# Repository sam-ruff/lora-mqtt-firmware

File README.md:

# LoRaMqttHub

Firmware that turns the Walkie-Textie radio board (ESP32-S3 + Wio-SX1262) into
a mains-powered hub. It has two operating modes, selected by configuration:

- **Bridge**: receives Walkie-Textie LoRa packets and publishes them to an
  MQTT broker over WiFi, and transmits packets published to its command topic.
- **LoRaWAN gateway**: a single-channel Semtech UDP packet forwarder for a
  LoRaWAN network server such as ChirpStack.

Pure Rust, no C: esp-hal + esp-rtos (Embassy executor), esp-radio for WiFi,
a hand-written SX1262 driver, embassy-net and rust-mqtt. The shared wire
protocol lives in the [`wt-protocol`](https://github.com/sam-ruff/walkie-textie-protocol)
submodule, so clone with `--recursive`.

## Building and flashing

```bash
cargo install espup espflash
espup install
source "$HOME/export-esp.sh"

cargo +esp build --features embedded --release -Zbuild-std=core,alloc
./flash_devices.sh          # build + flash all connected boards
```

After flashing, power-cycle the board (unplug and replug, do not hold BOOT).
The ESP32-S3 native USB-Serial-JTAG cannot be reset into the application from
the host, so the board stays in ROM download mode until power-cycled. A
running hub enumerates as "LoRaMqttHub" with USB serial `LMH-XXXXXX`
and exposes two CDC ports: data (interface 0) and debug log (interface 2).
The running app owns the USB port, so reflashing needs the board back in
bootloader mode first (hold BOOT while plugging in).

espflash reads `espflash.toml` from the working directory. If it names a
bootloader binary that does not exist, flashing fails with a misleading
"Error while connecting to device" - the file ships with the override
commented out and the stock espflash bootloader is used.

## Configuration

An unprovisioned hub (no WiFi credentials) starts its own open hotspot,
`LoRaMqttHub-XXXXXX`. Join it with a phone and the captive portal at
`http://192.168.4.1` opens: set the WiFi network, MQTT broker, operating mode
and gateway settings, save, and the hub restarts onto your network. The same
portal appears again if the configured network stays unreachable (wrong
password, network gone), so a hub can always be re-provisioned without a
cable. The portal also serves a JSON API (`GET/POST /api/config`,
`GET /api/status`) for app-driven setup.

Defaults can also be baked at build time through environment variables, all
optional: `HUB_WIFI_SSID`, `HUB_WIFI_PASSWORD`, `HUB_MQTT_HOST`,
`HUB_MQTT_PORT`, `HUB_MQTT_CLIENT_ID`, `HUB_MODE` (`bridge` or `gateway`),
`HUB_GW_HOST`, `HUB_GW_PORT`.

Runtime provisioning also works over the USB data port with hub commands
layered on the Walkie-Textie wire protocol (COBS-framed, CRC-16, see
`hub-protocol/`): set WiFi credentials, MQTT broker, gateway settings and
mode; read back the configuration (the WiFi password is never echoed) and
live status (link states, IP, counters, uptime). Settings persist in the
`nvs` flash partition and apply on the next boot, so the flow is set, then
reboot.

## Bridge mode

Topics live under `wt/hub/<id>/` where `<id>` is the hex device id from the
USB serial:

- `rx`: received LoRa packets, JSON with `payload_hex`, `rssi`, `snr`, `seq`
  and `uptime_ms`.
- `tx`: publish `{"payload_hex":"...","id":123}` here to transmit over LoRa;
  `id` is optional and echoed back.
- `tx/result`: `{"result":"sent"|"refused"|"error"...}` per downlink, with
  `retry_after_secs` when the EU duty cycle budget refuses a transmission.
- `status`: retained `{"online":true,...}`, with an offline last-will.

The broker connection is plain TCP (local broker assumed); the client id
defaults to `wt-hub-<id>`.

## LoRaWAN gateway mode

Speaks the Semtech UDP packet-forwarder protocol to a network server -
typically the ChirpStack gateway bridge on port 1700. The gateway EUI derives
from the MAC address with the standard FFFE insertion.

An SX1262 is a single-channel, half-duplex radio, which makes this a
single-channel gateway with real limitations:

- Only uplinks on the configured frequency and spreading factor are heard
  (default 868.1 MHz, SF7BW125). OTAA joins hop across three channels, so
  pin devices to the gateway channel and disable ADR in the device profile.
- The radio is deaf while transmitting a downlink.
- The Things Network discourages single-channel gateways; use a self-hosted
  ChirpStack.

Downlinks obey the EU duty cycle per sub-band and are refused with a
`DUTY_CYCLE_OVERFLOW` TX_ACK when the hourly budget is spent. The gateway is
payload-agnostic: joins, MICs and encryption all happen at the network server.

## Configurator app

`app/` holds a Flutter app for phones that drives the same provisioning API
as the captive portal: join the hub's hotspot, open the app, connect and set
everything up. The HTTP client and validation live in a Rust engine
(`app/rust_backend/`) exposed through flutter_rust_bridge, mirroring the
Walkie-Textie messenger app's architecture: `./build_rust.sh` regenerates the
bindings and builds the engine, Android cross-compiles it via cargo-ndk from
Gradle, and iOS links a static xcframework built by `tool/build_ios_libs.sh`.

```bash
cd app
./build_rust.sh
flutter run --dart-define=MOCK=true    # full flow against a fake hub, no hardware
flutter run                            # against a real hub
```

## Testing

Host tests need no hardware:

```bash
cargo test --features host-test --target x86_64-unknown-linux-gnu
cargo test --manifest-path hub-protocol/Cargo.toml --target x86_64-unknown-linux-gnu
cargo test --manifest-path vendor/wt-protocol/Cargo.toml --target x86_64-unknown-linux-gnu
```

Hardware tests run from `integration_tests/` against flashed boards:

```bash
cargo integration     # serial host-link, one board
cargo lora            # two boards over the air
cargo duty            # duty cycle lockout (spends ~6 min of airtime)
cargo hub -- --wifi-ssid <ssid> --wifi-password <pw> --broker-host <ip>
cargo gateway -- --server-host <this machine's LAN IP>
```

`cargo hub` needs a hub board, a node board and a reachable MQTT broker; it
provisions the hub, then proves both bridge directions end to end.
`cargo gateway` binds the network-server side itself and verifies the
forwarder protocol against the live gateway. Watch the debug CDC port
(115200 baud) for the firmware's own view of events.

For a Bluetooth-only node, `cargo ble-e2e` exchanges real messages across
the whole chain (BLE to the node, LoRa over the air, hub, MQTT broker) in
both directions, with a soak loop and failure-path checks. `cargo
hub-status` prints the hub's live state over serial, and `--clear` factory
resets it back to the provisioning hotspot.

The browser-driven portal tests live in `e2e/`: `run_e2e.sh` joins the
hub's hotspot with nmcli, runs the Playwright suite on desktop and mobile
viewports, provisions the hub through the real UI and rejoins your network.

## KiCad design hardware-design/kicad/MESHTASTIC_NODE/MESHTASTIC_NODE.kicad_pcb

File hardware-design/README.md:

# Hardware design

PCB design and tooling for the MESHTASTIC NODE board (ESP32-S3 + Wio-SX1262 LoRa).
There are two design states:

- `Production Files/` - the original as-built 4-layer manufacturing outputs. Send
  these straight to a fab if you just want the existing board made.
- `kicad/MESHTASTIC_NODE/` - an editable 4-layer KiCad project, generated entirely
  from scripts in `tools/` so a schematic edit reproduces a full production package.

Generated views live in `diagrams/`, component datasheets and a spec digest in
`datasheets/`, and helper scripts in `tools/`.

## Schematic-to-production pipeline

The whole flow is one command (needs the KiCad AppImage and the freerouting jar -
see "Routing toolchain" below):

```bash
python3 tools/build_all.py            # schematic -> board -> route -> kicad/fab/
```

It runs, and gates on, each stage: regenerate the schematic
(`build_schematic.py`), ERC, verify every firmware net (`verify_nets.py`), build
the 4-layer board (`board_setup.py` + `build_board.py`), check placement
(`check_placement.py`), autoroute + finish + pour ground/power planes
(`route.py`), DRC (must be 0 errors / 0 unconnected / parity-clean), then export
the Gerbers, drill, CPL and BOM (`fab_outputs.py`). Upload
`kicad/fab/gerbers.zip` plus `BOM.csv` and `CPL.csv` to PCBWay.

To change the board, edit the net map in `tools/build_schematic.py` (and the
placement overrides in `tools/placement.py` if a part needs moving), then re-run
`build_all.py`. Use `--skip-route` to re-check and re-export the current routed
board without re-routing.

### Routing toolchain

`tools/route.py` exports a Specctra DSN with the bundled `pcbnew`, autoroutes the
signals with freerouting (headless), imports the SES back, closes any stragglers
(`finish_route.py`), then pours the GND/+3V3 planes and stitching vias
(`pour.py`). Install freerouting once:

```bash
mkdir -p ~/.local/share/freerouting
curl -L -o ~/.local/share/freerouting/freerouting-2.2.4.jar \
  https://github.com/freerouting/freerouting/releases/download/v2.2.4/freerouting-2.2.4.jar
```

Override the tool paths with the `KICAD_APPIMAGE` and `FREEROUTING_JAR` env vars.

## Tools to install first

Commands assume Ubuntu Linux. `uv` and Node.js are expected to be present already.

### KiCad 9 or newer (required)

Provides `kicad-cli`, the GUI editors, and the bundled ngspice/3D tools. The
design was authored in 9.0.1, and the headless DRC/ERC checks need v9+; KiCad 7
(the default in some Ubuntu repos) cannot open v9 files or run the CLI checks.

```bash
# option 1 - PPA (needs sudo)
sudo add-apt-repository ppa:kicad/kicad-9.0-releases
sudo apt update && sudo apt install --install-recommends kicad

# option 2 - Flatpak (no sudo)
flatpak install --user flathub org.kicad.KiCad
flatpak run --command=kicad-cli org.kicad.KiCad version

# option 3 - AppImage (no sudo) - the method in use here
# download the KiCad AppImage, put it on a writeable PATH dir, and add a wrapper
# that dispatches the bundled CLI (the AppImage selects its tool from the first arg):
mv kicad-*-x86_64.AppImage ~/.local/bin/ && chmod +x ~/.local/bin/kicad-*.AppImage
printf '#!/bin/sh\nexec "$HOME/.local/bin/kicad-10.0.3-x86_64.AppImage" kicad-cli "$@"\n' > ~/.local/bin/kicad-cli
printf '#!/bin/sh\nexec "$HOME/.local/bin/kicad-10.0.3-x86_64.AppImage" kicad "$@"\n' > ~/.local/bin/kicad
chmod +x ~/.local/bin/kicad-cli ~/.local/bin/kicad
```

For headless 3D board renders also install `xvfb`.

### Diagram rendering

```bash
# block / component-overview diagrams (needs Node.js + Chrome/Chromium)
npm install -g @mermaid-js/mermaid-cli
# rendering points Puppeteer at the system Chrome via tools/puppeteer-config.json

# to-scale placement diagram
uv pip install matplotlib
```

### Gerber inspection (no KiCad source needed)

```bash
uv tool install gerbonara      # render Gerbers to SVG
uvx cairosvg in.svg -o out.png -s 3   # rasterise SVG to PNG so it can be viewed
```

## Regenerating diagrams

See the top-level `CLAUDE.md` for the regeneration commands and the readability
checklist that must pass before a diagram change is considered done.

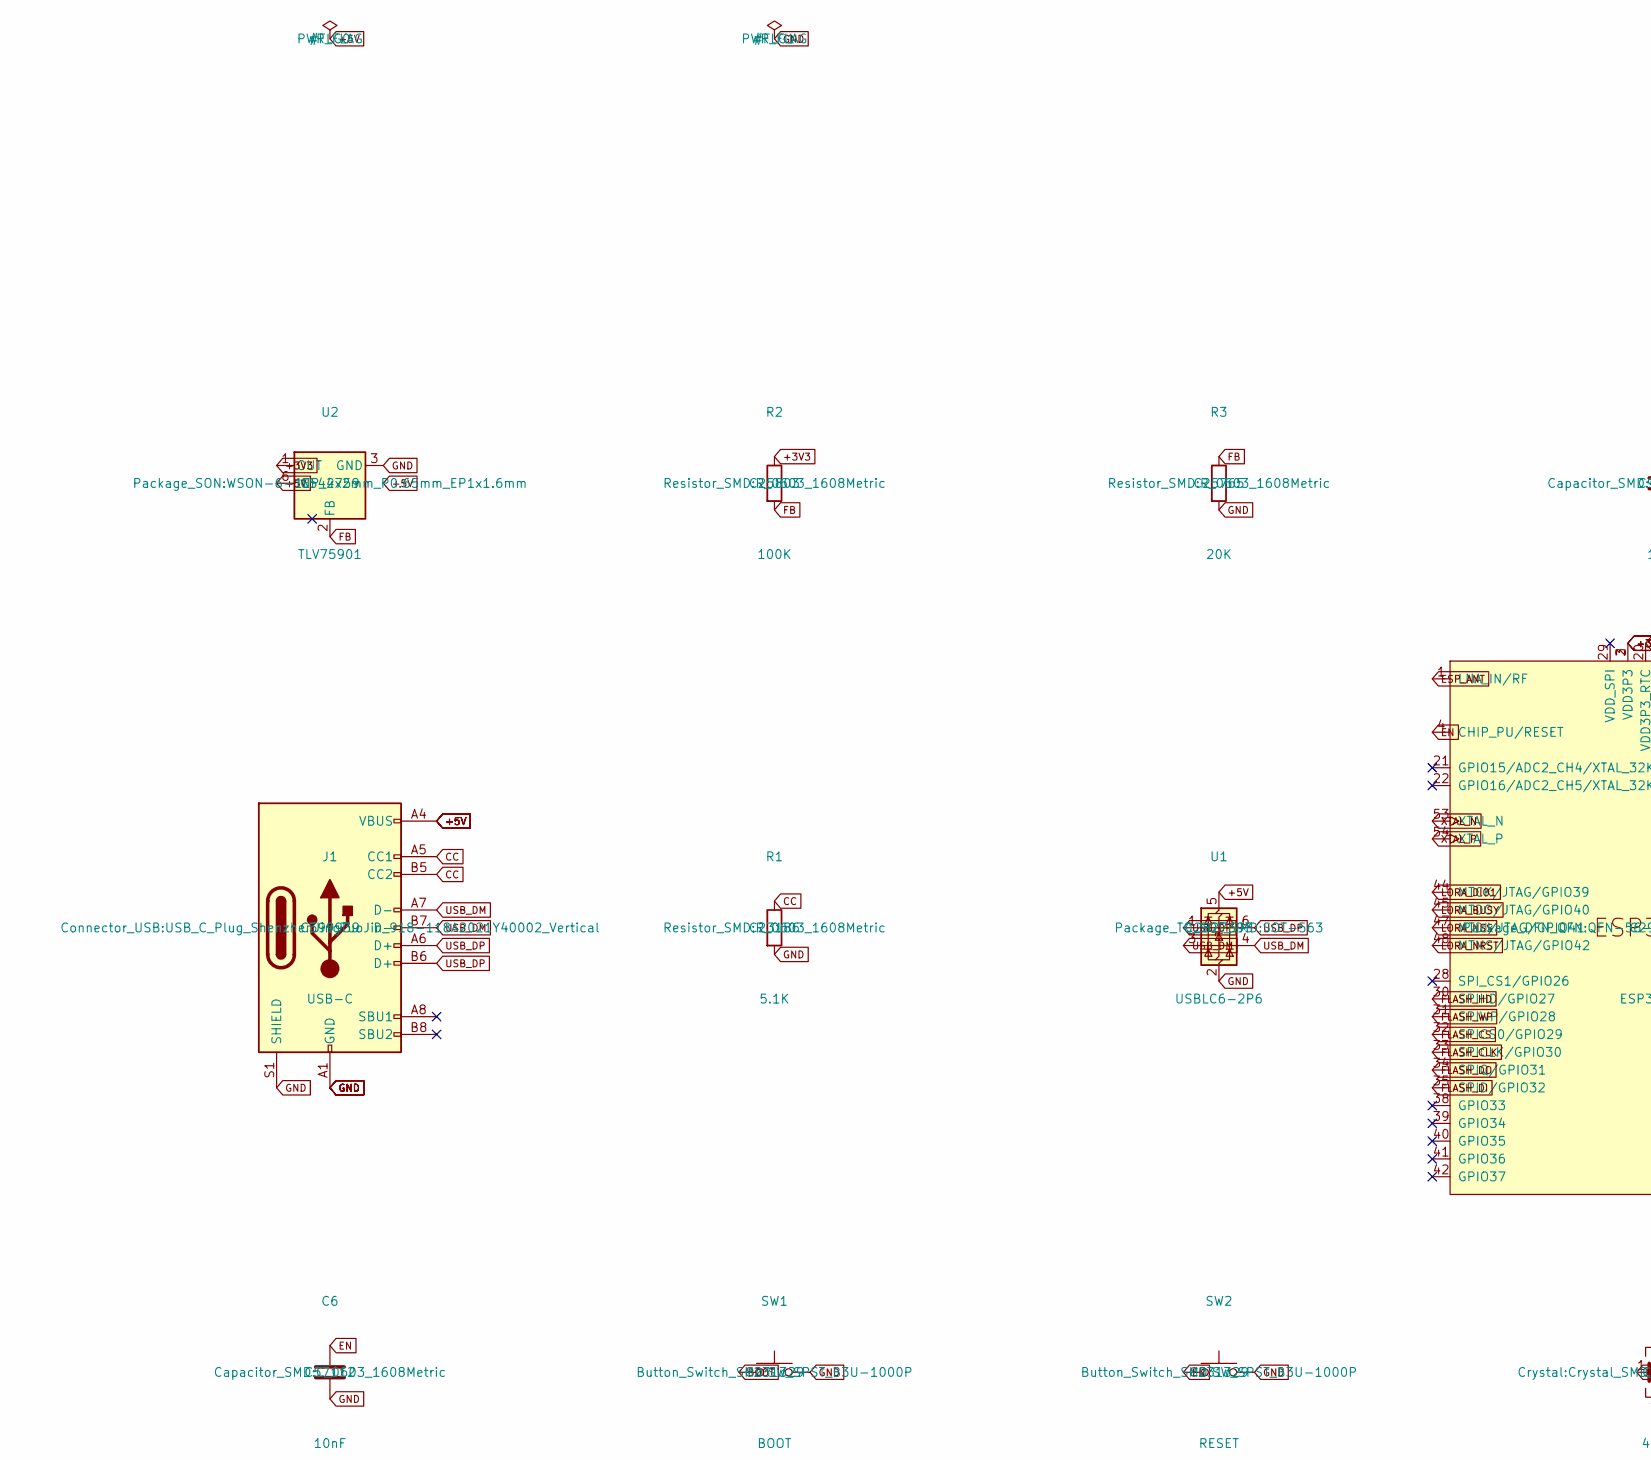
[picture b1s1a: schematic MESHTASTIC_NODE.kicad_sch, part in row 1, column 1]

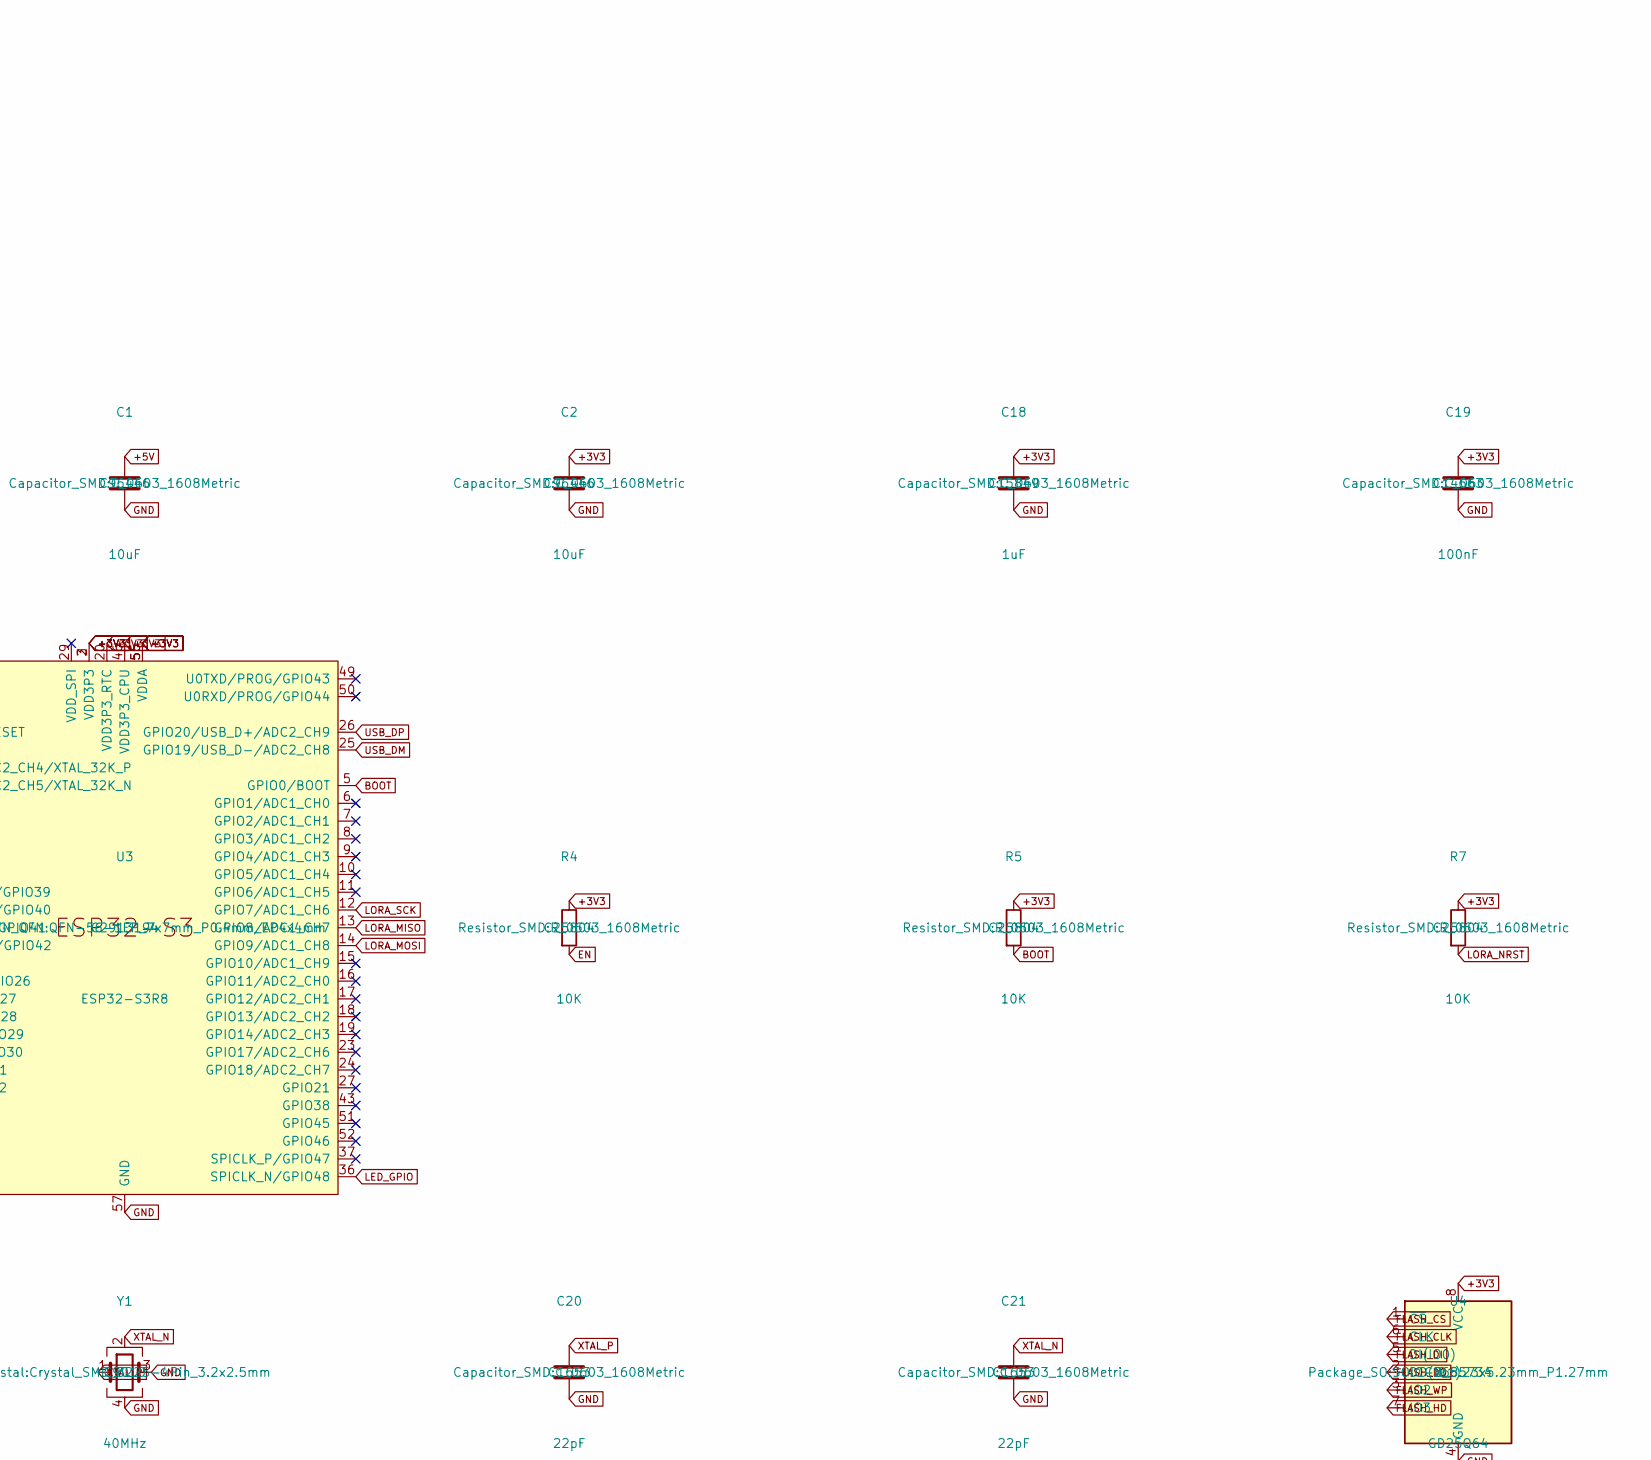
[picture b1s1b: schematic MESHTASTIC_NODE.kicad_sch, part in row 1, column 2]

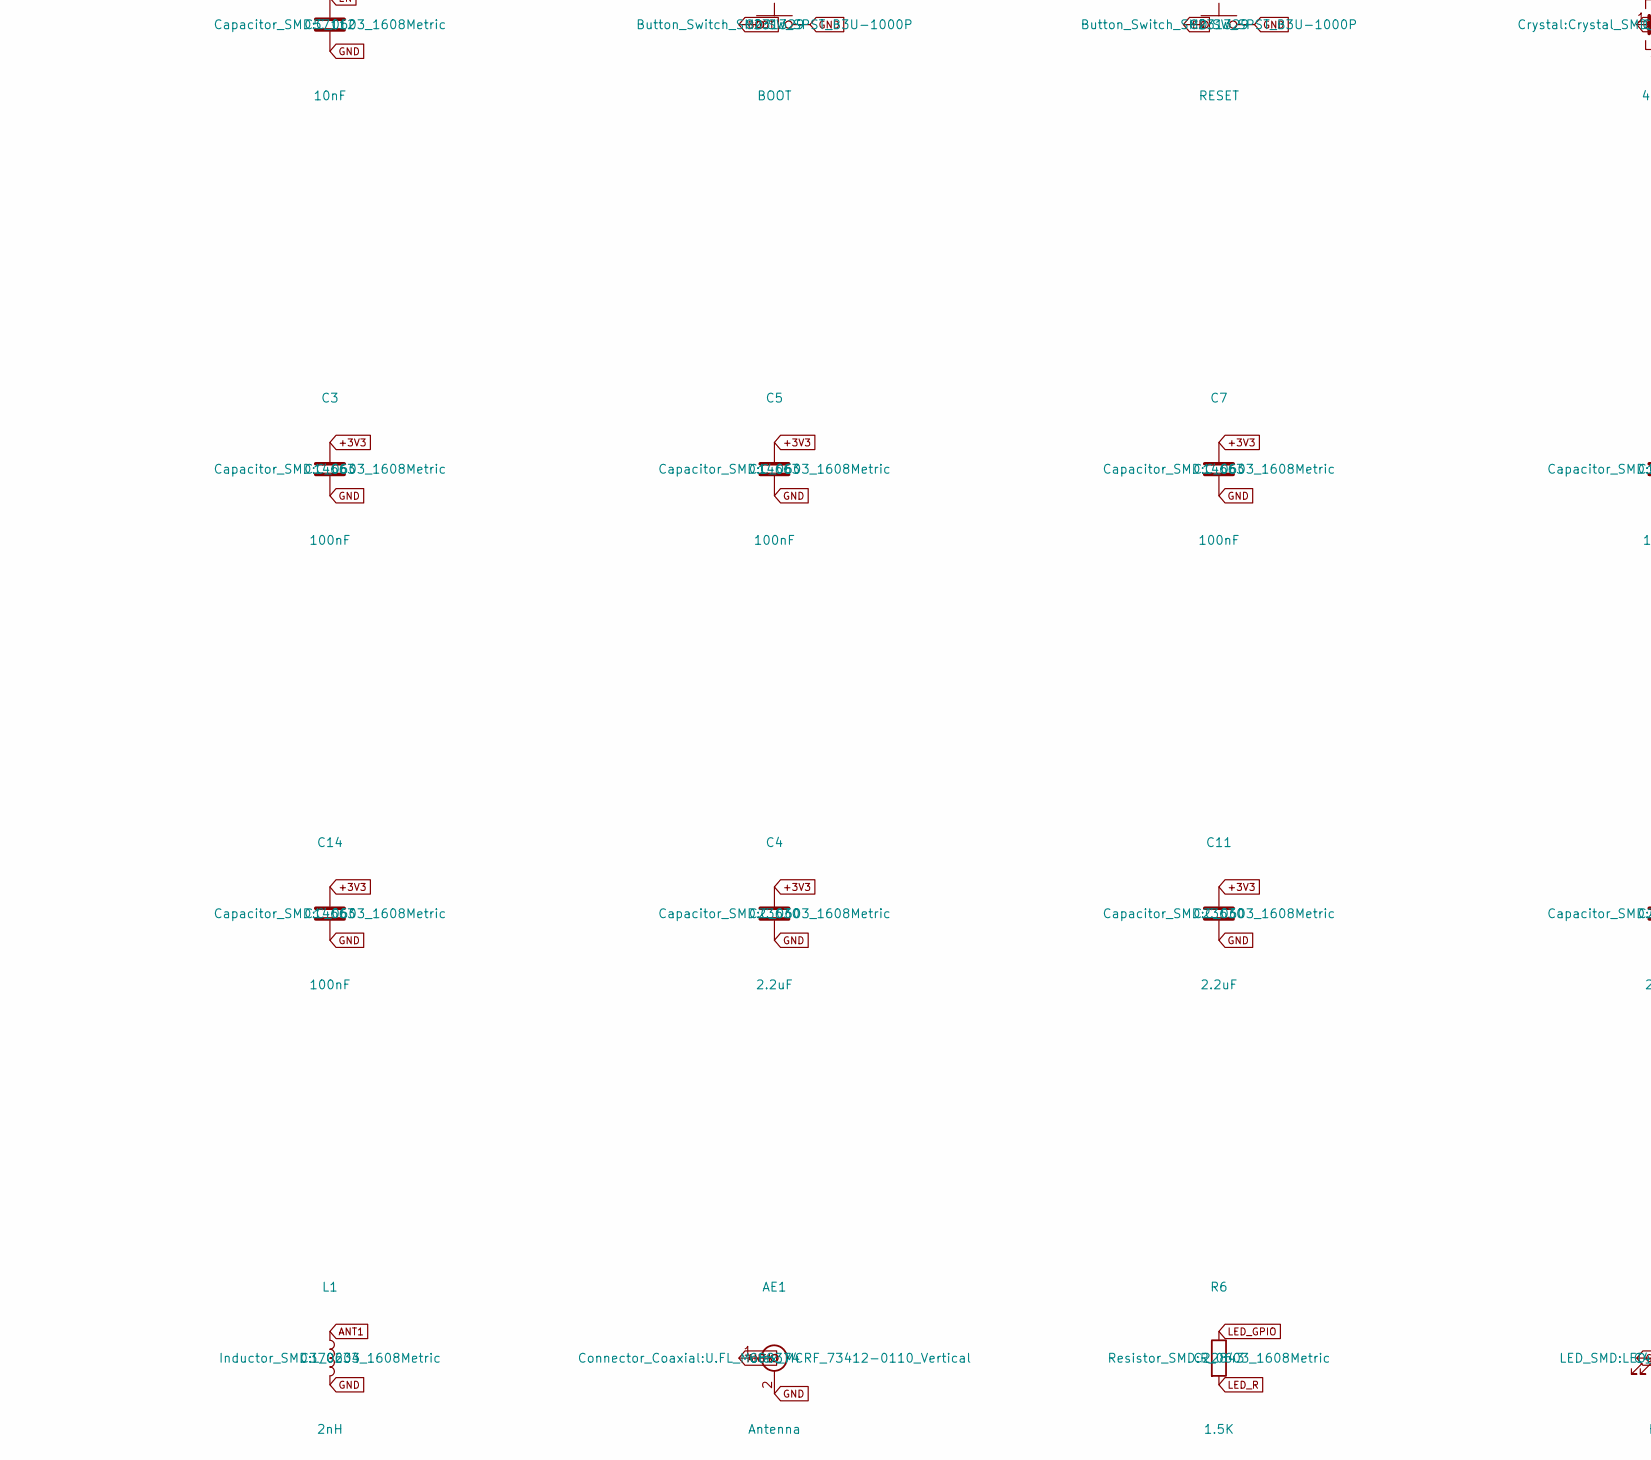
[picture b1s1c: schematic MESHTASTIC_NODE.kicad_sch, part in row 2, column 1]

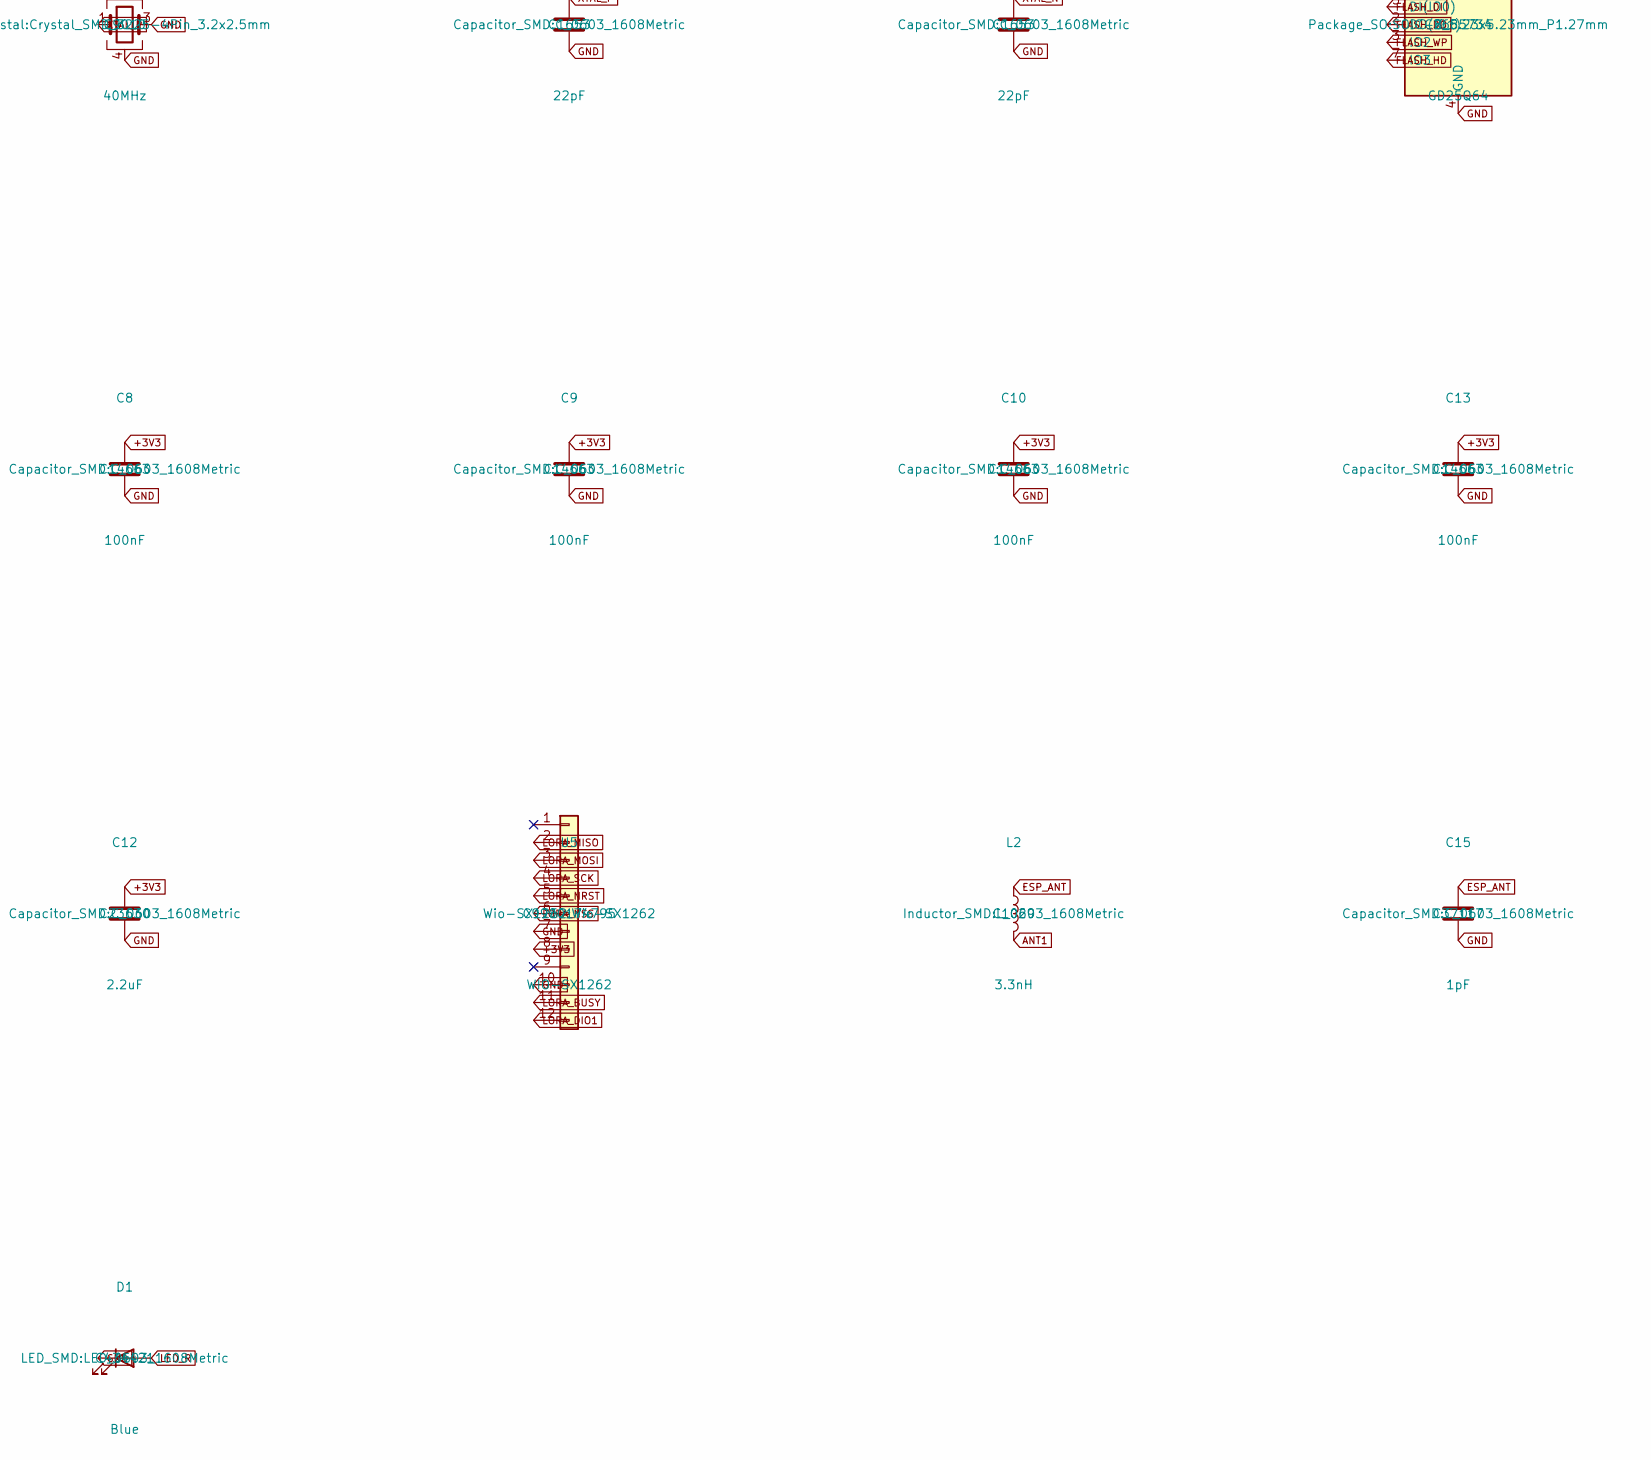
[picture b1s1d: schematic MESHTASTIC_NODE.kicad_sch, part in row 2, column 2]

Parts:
AE1: Antenna; U.FL_Molex_MCRF_73412-0110_Vertical; LCSC C88374
C1, C2: 10uF; C_0603_1608Metric; LCSC C96446
C3, C5, C7, C8, C9, C10, C13, C14, C19: 100nF; C_0603_1608Metric; LCSC C14663
C4, C11, C12: 2.2uF; C_0603_1608Metric; LCSC C23630
C6: 10nF; C_0603_1608Metric; LCSC C57112
C15: 1pF; C_0603_1608Metric; LCSC C37117
C18: 1uF; C_0603_1608Metric; LCSC C15849
C20, C21: 22pF; C_0603_1608Metric; LCSC C1653
D1: Blue; LED_0603_1608Metric; LCSC C434421
J1: USB-C; USB_C_Plug_ShenzhenJingTuoJin_918-118A2021Y40002_Vertical; LCSC C399939
L1: 2nH; L_0603_1608Metric; LCSC C370234
L2: 3.3nH; L_0603_1608Metric; LCSC C1029
R1: 5.1K; R_0603_1608Metric; LCSC C23186
R2: 100K; R_0603_1608Metric; LCSC C25803
R3: 20K; R_0603_1608Metric; LCSC C25765
R4, R5, R7: 10K; R_0603_1608Metric; LCSC C25804
R6: 1.5K; R_0603_1608Metric; LCSC C22843
SW1: BOOT; SW_SPST_B3U-1000P; LCSC C231329
SW2: RESET; SW_SPST_B3U-1000P; LCSC C231329
U1: USBLC6-2P6; SOT-563; LCSC C2827693
U2: TLV75901; WSON-6-1EP_2x2mm_P0.65mm_EP1x1.6mm; LCSC C544759
U3: ESP32-S3R8; QFN-56-1EP_7x7mm_P0.4mm_EP4x4mm; LCSC C2913194
U4: GD25Q64; SOIC-8_5.23x5.23mm_P1.27mm; LCSC C2685734
U5: WIO-SX1262; Wio-SX1262; LCSC C9900174795
Y1: 40MHz; Crystal_SMD_3225-4Pin_3.2x2.5mm; LCSC C9010

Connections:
+3V3: C2.1, C3.1, C4.1, C5.1, C7.1, C8.1, C9.1, C10.1, C11.1, C12.1, C13.1, C14.1, C18.1, C19.1, R2.1, R4.1, R5.1, R7.1, U2.1 (OUT), U3.2 (VDD3P3), U3.3 (VDD3P3), U3.20 (VDD3P3_RTC), U3.46 (VDD3P3_CPU), U3.55 (VDDA), U3.56 (VDDA), U4.8 (VCC), U5.8 (VCC)
+5V: C1.1, J1.A4 (VBUS), J1.A9 (VBUS), J1.B4 (VBUS), J1.B9 (VBUS), U1.5 (VBUS), U2.4 (EN), U2.6 (IN)
ANT1: AE1.1 (In), L1.1, L2.2
BOOT: R5.2, SW1.1, U3.5 (GPIO0/BOOT)
CC: J1.A5 (CC1), J1.B5 (CC2), R1.1
EN: C6.1, R4.2, SW2.1, U3.4 (CHIP_PU/RESET)
ESP_ANT: C15.1, L2.1, U3.1 (LNA_IN/RF)
FB: R2.2, R3.1, U2.2 (FB)
FLASH_CLK: U3.33 (SPICLK/GPIO30), U4.6 (CLK)
FLASH_CS: U3.32 (SPICS0/GPIO29), U4.1 (~CS)
FLASH_DI: U3.35 (SPID/GPIO32), U4.5 (DI(IO0))
FLASH_DO: U3.34 (SPIQ/GPIO31), U4.2 (DO(IO1))
FLASH_HD: U3.30 (SPIHD/GPIO27), U4.7 (IO3)
FLASH_WP: U3.31 (SPIWP/GPIO28), U4.3 (IO2)
GND: AE1.2 (Ext), C1.2, C2.2, C3.2, C4.2, C5.2, C6.2, C7.2, C8.2, C9.2, C10.2, C11.2, C12.2, C13.2, C14.2, C15.2, C18.2, C19.2, C20.2, C21.2, D1.1 (K), J1.A1 (GND), J1.A12 (GND), J1.B1 (GND), J1.B12 (GND), J1.S1 (SHIELD), L1.2, R1.2, R3.2, SW1.2, SW2.2, U1.2 (GND), U2.3 (GND), U3.57 (GND), U4.4 (GND), U5.7 (GND1), U5.10 (GND2), Y1.3, Y1.4
LED_GPIO: R6.1, U3.36 (SPICLK_N/GPIO48)
LED_R: D1.2 (A), R6.2
LORA_BUSY: U3.45 (MTDO/JTAG/GPIO40), U5.11 (BUSY)
LORA_DIO1: U3.44 (MTCK/JTAG/GPIO39), U5.12 (DIO1)
LORA_MISO: U3.13 (GPIO8/ADC1_CH7), U5.2 (MISO)
LORA_MOSI: U3.14 (GPIO9/ADC1_CH8), U5.3 (MOSI)
LORA_NRST: R7.2, U3.48 (MTMS/JTAG/GPIO42), U5.5 (RST)
LORA_NSS: U3.47 (MTDI/JTAG/GPIO41), U5.6 (NSS)
LORA_SCK: U3.12 (GPIO7/ADC1_CH6), U5.4 (SCK)
USB_DM: J1.A7 (D-), J1.B7 (D-), U1.3 (I/O2), U1.4 (I/O2), U3.25 (GPIO19/USB_D-/ADC2_CH8)
USB_DP: J1.A6 (D+), J1.B6 (D+), U1.1 (I/O1), U1.6 (I/O1), U3.26 (GPIO20/USB_D+/ADC2_CH9)
XTAL_N: C21.1, U3.53 (XTAL_N), Y1.2
XTAL_P: C20.1, U3.54 (XTAL_P), Y1.1

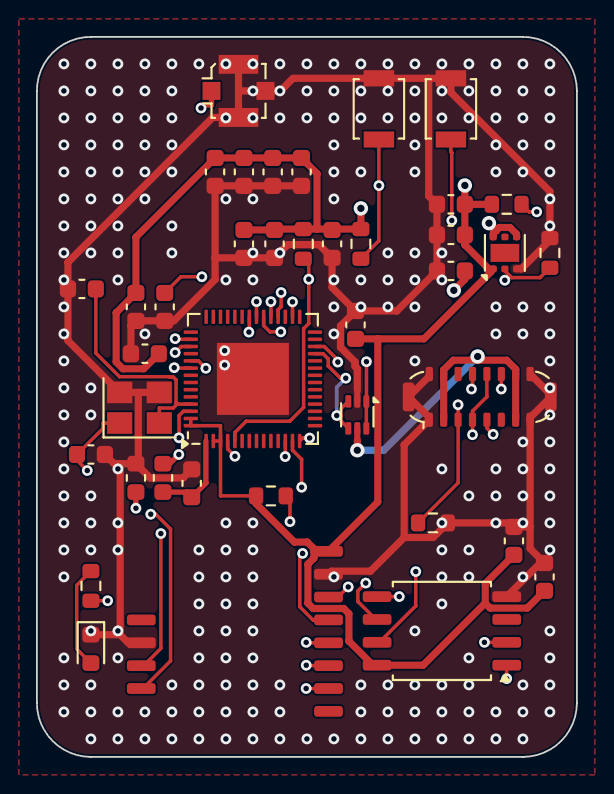
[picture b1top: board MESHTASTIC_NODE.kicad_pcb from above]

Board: 4 copper layers, 30.0 x 40.0 mm, 39 parts (0 on the bottom side), 28 nets.

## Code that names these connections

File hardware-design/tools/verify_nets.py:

"""Check captured schematic nets against the firmware pin map (ground truth).

Exports the netlist with kicad-cli and asserts that the connections defined in the
firmware (src/main.rs) are present. Run after schematic capture. If you name nets
differently during capture, update EXPECTED below (matching is by substring, so a
label like /LORA_NSS still matches the key LORA_NSS).
"""

from __future__ import annotations

import re
import subprocess
import sys
from pathlib import Path

ROOT = Path(__file__).resolve().parent.parent
SCH = ROOT / "kicad" / "MESHTASTIC_NODE" / "MESHTASTIC_NODE.kicad_sch"
NET = Path("/tmp/meshtastic_node.net")

# Net name (substring) -> reference designators that must share that net.
# Derived from src/main.rs: SCLK=GPIO7, MISO=GPIO8, MOSI=GPIO9, NSS=GPIO41,
# DIO1=GPIO39, NRST=GPIO42, BUSY=GPIO40; USB D+=GPIO20, D-=GPIO19; LED=GPIO48.
EXPECTED: dict[str, set[str]] = {
    "3V3": {"U2", "U3", "U4", "U5"},
    "LORA_NSS": {"U3", "U5"},
    "LORA_SCK": {"U3", "U5"},
    "LORA_MOSI": {"U3", "U5"},
    "LORA_MISO": {"U3", "U5"},
    "LORA_BUSY": {"U3", "U5"},
    "LORA_DIO1": {"U3", "U5"},
    "LORA_NRST": {"U3", "U5"},
    "USB_DP": {"J1", "U1", "U3"},
    "USB_DM": {"J1", "U1", "U3"},
    "LED_GPIO": {"U3", "R6"},   # GPIO48 -> series resistor
    "LED_R": {"R6", "D1"},      # resistor -> LED
}


def export_netlist() -> str:
    subprocess.run(
        ["kicad-cli", "sch", "export", "netlist", "--output", str(NET), str(SCH)],
        check=True,
    )
    return NET.read_text()


def parse_nets(text: str) -> dict[str, set[str]]:
    nets: dict[str, set[str]] = {}
    for chunk in re.split(r"\(net\b", text)[1:]:
        name_m = re.search(r'\(name\s+"?([^"\)\s]+)"?\)', chunk)
        if not name_m:
            continue
        refs = set(re.findall(r'\(ref\s+"?([^"\s\)]+)"?\)', chunk))
        nets[name_m.group(1)] = refs
    return nets


def main() -> int:
    text = export_netlist()
    nets = parse_nets(text)
    ok = True
    for key, want in EXPECTED.items():
        match = next((r for n, r in nets.items() if key.lower() in n.lower()), None)
        if match is None:
            print(f"FAIL {key}: no net found")
            ok = False
            continue
        missing = want - match
        if missing:
            print(f"FAIL {key}: missing {sorted(missing)} (has {sorted(match)})")
            ok = False
        else:
            print(f"ok   {key}: {sorted(match & want)}")
    print("all firmware nets present" if ok else "net verification FAILED")
    return 0 if ok else 1


if __name__ == "__main__":
    sys.exit(main())

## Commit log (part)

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2025-12-06 feat(api): initial commit
2025-12-06 Removed target directory
2025-12-06 fix: Updated rust action
2025-12-06 fix: Updated README and made actions skip on chores
2025-12-06 fix: Working BLE implementation and tests
2025-12-06 fix: Made the recieving more reliable and added ble to ble tests
2025-12-14 fix: Minor fixes
2025-12-14 fix: Moved embassy tasks to tasks module
2025-12-14 fix: Working debug logging
2025-12-15 fix: Added debug for version and reboot command and fixed github actions.
2025-12-15 fix: updated README with commands
2025-12-15 fix: Fixed a number of warnings and made clippy happy
2025-12-15 fix: Removed serial module
2025-12-15 fix: Fixed some missing packages and removed log
2025-12-15 fix: Updated how debugging works
2025-12-15 fix: Updated tests and flash devices
2026-06-19 chore(lora): WIP calibration and driver updates
2026-06-19 refactor(protocol): use shared wt-protocol crate for the wire codec
    Replace the in-tree commands/ and protocol/ modules with the shared
    wt-protocol crate, vendored as a git submodule, so the firmware and the
    phone app share one COBS/CRC command-response codec and cannot drift.
    - swap CommandParser/ResponseSerialiser for wt_protocol::{parse_command,
    encode_response, cobs_decode} in the serial and BLE tasks
    - FrameAccumulator now yields frames including the trailing delimiter,
